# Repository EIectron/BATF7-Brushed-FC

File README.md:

# BATF7-Brushed-FC
 STM32F722 Based brushed flight controller board

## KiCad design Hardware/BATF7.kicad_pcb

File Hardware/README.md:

<div align="center">
  <b>
   <h1>
      BATF7
   </h1>
   <h6>
     V1
   </h6>
  </b>

</div>

Key Features
* ARM Cortex-M7 core F7 216 MHz CPU
* Invensense MPU-6500 Six-Axis (Gyro + Accelerometer) low power consumption MEMS MotionTracking™ Device
* Blackbox logging via onboard dataflash chip
* Battery polarity reversed connection protection. The fc board remains perfect even if you plug the battery in wrong way.
* Fully programmable through Betaflight, using the onboard USB port, tune all the parameters, PID's, and rates to your perfect settings
* Designed to work with current Whoop Drone or Blade Inductrix setups
* The flight controller board comes pre-flashed with Betaflight firmware, and pre-soldered 55mm power cable pigtail with JST-PH 2.0 connector, AKA PowerWhoop connector.

Specifications
* CPU: `STM32F411CEU6`
* Six-Axis: `MPU6500`
* ESC: All FETs are rated at 35A maximum. Support 6x15mm/7x20mm/8x20mm/8.5x20mm etc motors.
* Size: 29mm x 29mm, fully compatible with the Inductrix quad frame and mounting pattern
* Firmware version: Betaflight BATF7 3.5.0
* Power Cable: 55mm, with JST-PH 2.0 connector, AKA PowerWhoop connector
* Weight: 4.2g

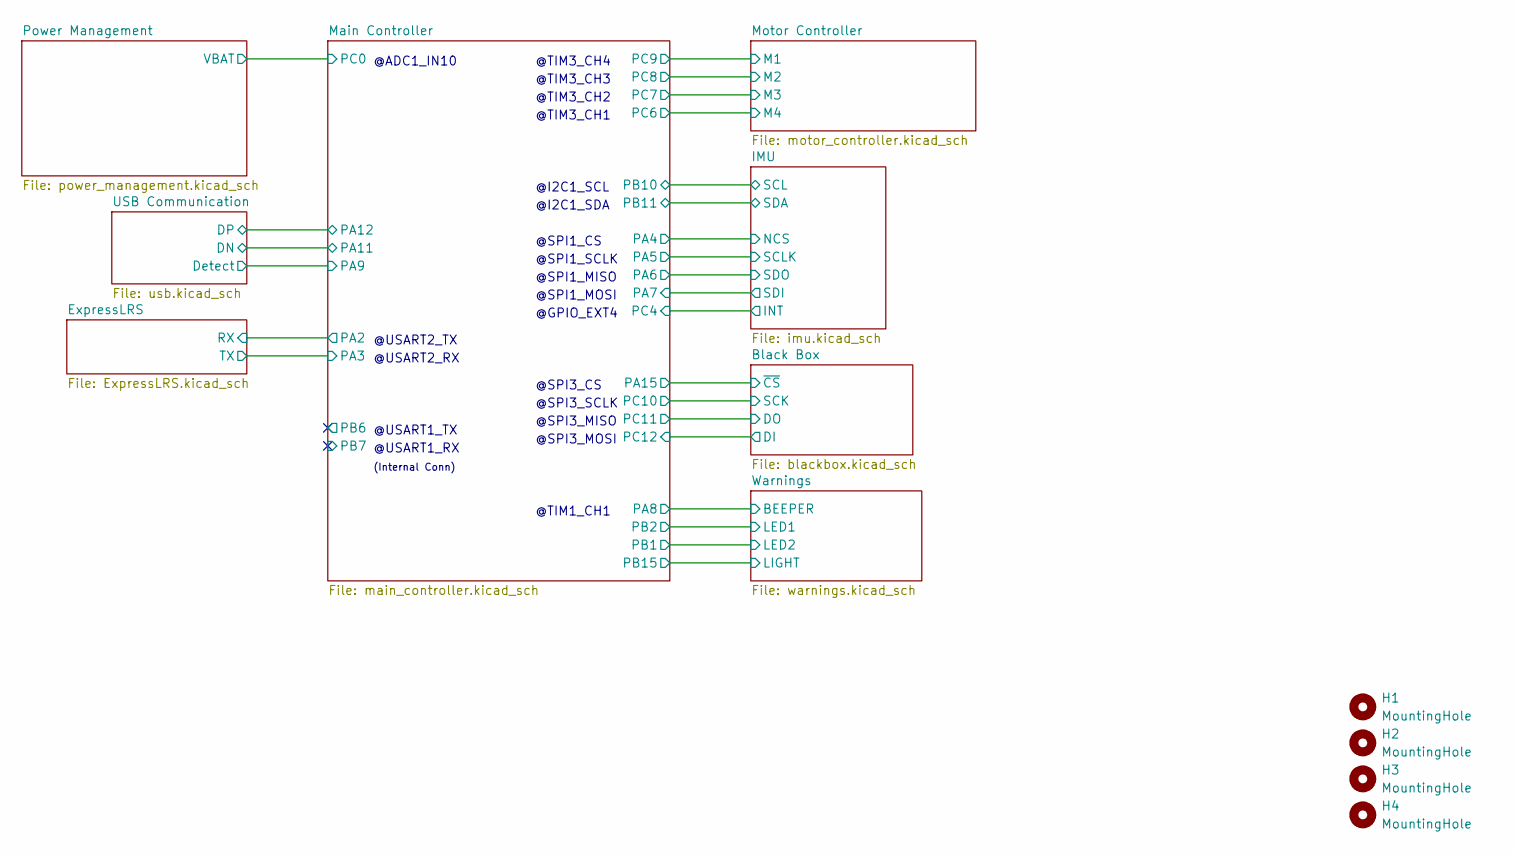
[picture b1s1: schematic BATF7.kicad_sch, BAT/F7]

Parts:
H1, H2, H3, H4: MountingHole; MH32

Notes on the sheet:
@ADC1_IN10
@USART1_RX
@TIM3_CH4
@USART2_TX
(Internal Conn)
@SPI3_SCLK
@USART1_TX
@TIM3_CH1
@SPI3_MOSI
@TIM1_CH1
@SPI3_MISO
@SPI1_MOSI
@I2C1_SDA
@TIM3_CH2
@I2C1_SCL
@SPI3_CS
@USART2_RX
@SPI1_MISO
@SPI1_CS
@TIM3_CH3
@SPI1_SCLK
@GPIO_EXT4

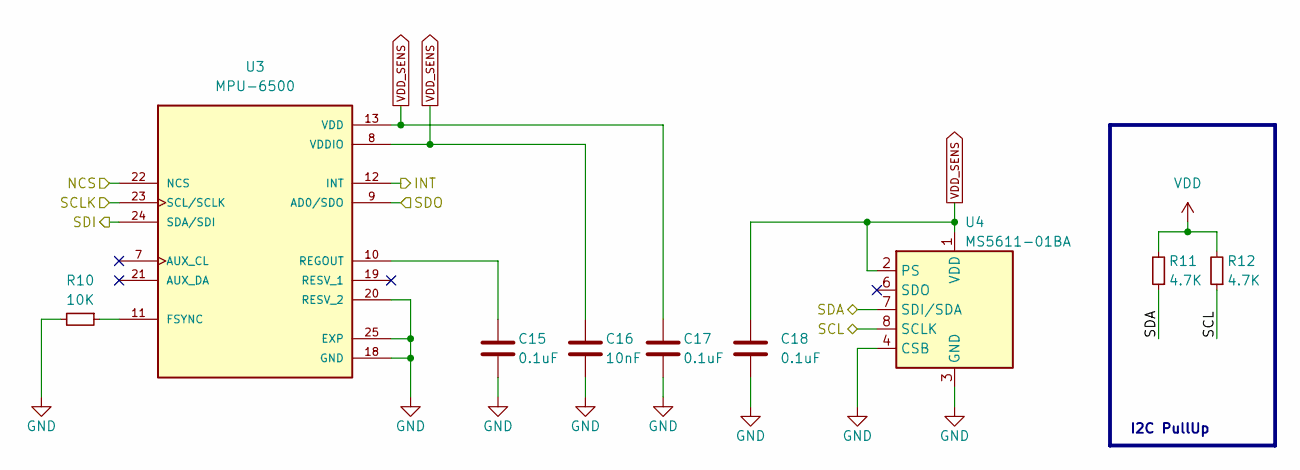
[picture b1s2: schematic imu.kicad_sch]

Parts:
C15, C17, C18: 0.1uF; C_0402_1005Metric
C16: 10nF; C_0402_1005Metric
R10: 10K; R_0402_1005Metric
R11, R12: 4.7K; R_0402_1005Metric
U3: MPU-6500; MPU6500
U4: MS5611-01BA; LGA-8_3x5mm_P1.25mm

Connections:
/IMU/SCL: R12.1, U4.8 (SCLK); also elsewhere on the board
/IMU/SDA: R11.1, U4.7 (SDI/SDA); also elsewhere on the board
/Main Controller/MPU_INT: U3.12 (INT); also elsewhere on the board
/Main Controller/SPI1_MISO: U3.9 (AD0/SDO); also elsewhere on the board
/Main Controller/SPI1_MOSI: U3.24 (SDA/SDI); also elsewhere on the board
/Main Controller/SPI1_SCK: U3.23 (SCL/SCLK); also elsewhere on the board
/Main Controller/SPI1_~CS: U3.22 (NCS); also elsewhere on the board
GND: C15.2, C16.1, C17.2, C18.2, R10.2, U3.18 (GND), U3.20 (RESV_2), U3.25 (EXP), U4.3 (GND), U4.4 (CSB), U4.5 (CSB); also elsewhere on the board
unnamed: R10.1, U3.11 (FSYNC)
unnamed: C15.1, U3.10 (REGOUT)
VDD: R11.2, R12.2; also elsewhere on the board
VDD_SENS: C16.2, C17.1, C18.1, U3.8 (VDDIO), U3.13 (VDD), U4.1 (VDD), U4.2 (PS); also elsewhere on the board

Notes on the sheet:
I2C PullUp

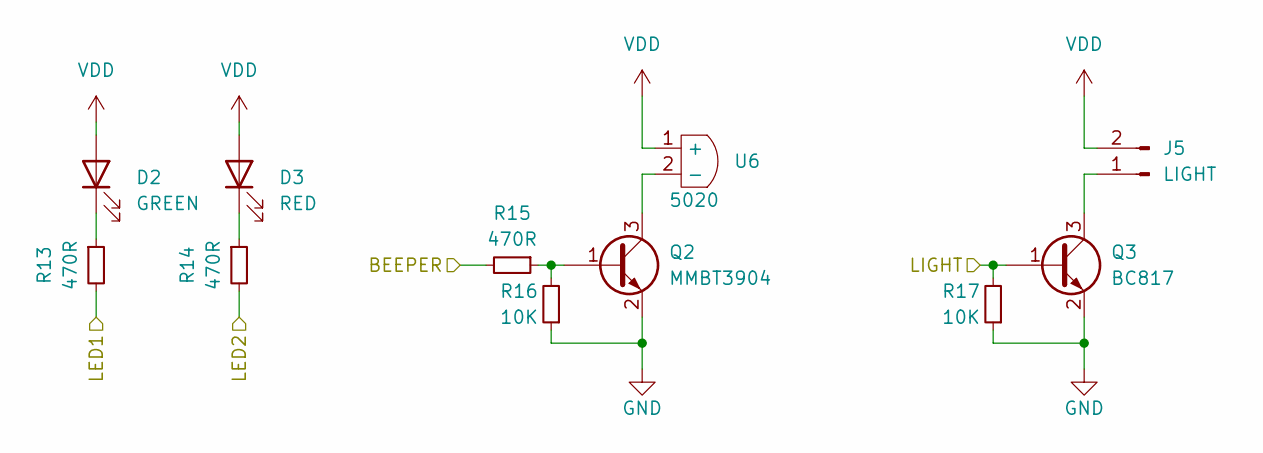
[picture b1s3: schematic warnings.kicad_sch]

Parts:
D2: GREEN; LED_0603_1608Metric
D3: RED; LED_0603_1608Metric
J5: LIGHT; C_0805_2012Metric
Q2: MMBT3904; SOT-23
Q3: BC817; SOT-23
R13, R14, R15: 470R; R_0402_1005Metric
R16, R17: 10K; R_0402_1005Metric
U6: 5020; ABMT-801-RC_PIEZO

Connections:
/Main Controller/BEEPER: R15.2; also elsewhere on the board
/Main Controller/LED1: R13.2; also elsewhere on the board
/Main Controller/LED2: R14.2; also elsewhere on the board
/Main Controller/LIGHT: Q3.1 (B), R17.2; also elsewhere on the board
GND: Q2.2 (E), Q3.2 (E), R16.1, R17.1; also elsewhere on the board
unnamed: D2.1 (K), R13.1
unnamed: D3.1 (K), R14.1
unnamed: J5.1, Q3.3 (C)
unnamed: Q2.1 (B), R15.1, R16.2
unnamed: Q2.3 (C), U6.2 (-)
VDD: D2.2 (A), D3.2 (A), J5.2, U6.1 (+); also elsewhere on the board

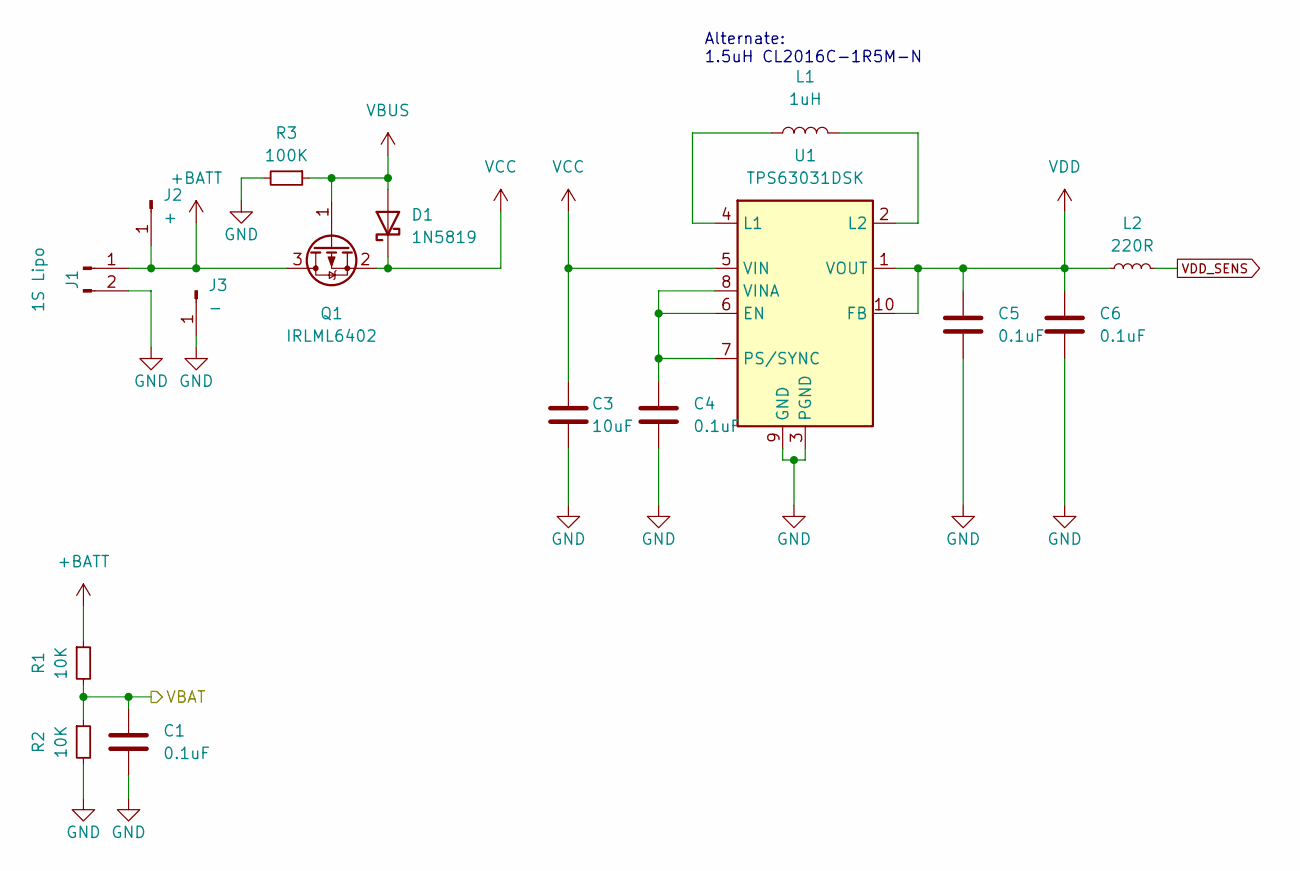
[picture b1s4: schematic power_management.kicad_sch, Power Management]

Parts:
C1, C4, C5, C6: 0.1uF; C_0402_1005Metric
C3: 10uF; C_0402_1005Metric
D1: 1N5819; SOD-323
J1: 1S Lipo; 1x02-Long-Pad
J2: +; TestPoint_THTPad_1.0x1.0mm_Drill0.5mm
J3: -; TestPoint_THTPad_1.0x1.0mm_Drill0.5mm
L1: 1uH; L_Murata_DFE201610P
L2: 220R; L_0603_1608Metric
Q1: IRLML6402; SOT-23
R1, R2: 10K; R_0402_1005Metric
R3: 100K; R_0402_1005Metric
U1: TPS63031DSK; WSON-10-1EP_2.5x2.5mm_P0.5mm_EP1.2x2mm

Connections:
+BATT: J1.1, J2.1, Q1.3 (D), R1.1; also elsewhere on the board
/Main Controller/VBAT_ADC: C1.1, R1.2, R2.1; also elsewhere on the board
GND: C1.2, C3.2, C4.2, C5.2, C6.2, J1.2, J3.1, R2.2, R3.2, U1.3 (PGND), U1.9 (GND), U1.11 (PGND); also elsewhere on the board
unnamed: C4.1, U1.6 (EN), U1.7 (PS/SYNC), U1.8 (VINA)
unnamed: L1.1, U1.4 (L1)
unnamed: L1.2, U1.2 (L2)
VBUS: D1.2 (A), Q1.1 (G), R3.1; also elsewhere on the board
VCC: C3.1, D1.1 (K), Q1.2 (S), U1.5 (VIN)
VDD: C5.1, C6.1, L2.1, U1.1 (VOUT), U1.10 (FB); also elsewhere on the board
VDD_SENS: L2.2; also elsewhere on the board

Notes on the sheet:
Alternate: 1.5uH CL2016C-1R5M-N

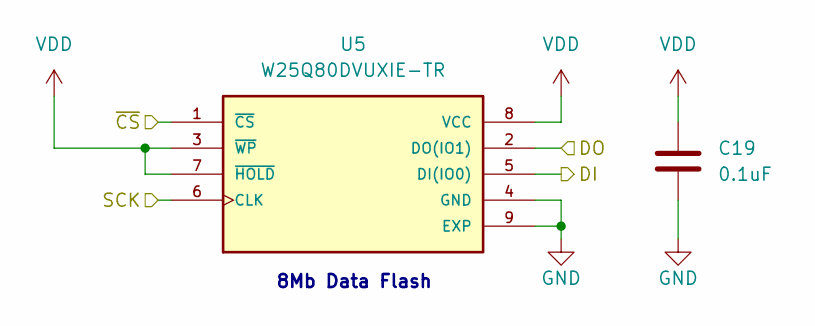
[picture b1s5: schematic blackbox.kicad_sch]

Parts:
C19: 0.1uF; C_0402_1005Metric
U5: W25Q80DVUXIE-TR; 8-USON

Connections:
/Main Controller/SPI3_MISO: U5.2 (DO(IO1)); also elsewhere on the board
/Main Controller/SPI3_MOSI: U5.5 (DI(IO0)); also elsewhere on the board
/Main Controller/SPI3_SCK: U5.6 (CLK); also elsewhere on the board
/Main Controller/SPI3_~CS: U5.1 (~CS); also elsewhere on the board
GND: C19.2, U5.4 (GND), U5.9 (EXP); also elsewhere on the board
VDD: C19.1, U5.3 (~WP), U5.7 (~HOLD), U5.8 (VCC); also elsewhere on the board

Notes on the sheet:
8Mb Data Flash

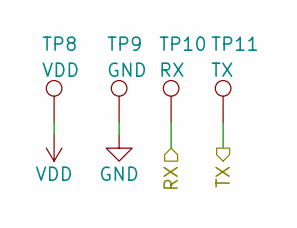
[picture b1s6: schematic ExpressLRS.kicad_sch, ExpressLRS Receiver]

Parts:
TP8: VDD; TestPoint_Pad_1.0x1.0mm
TP9: GND; TestPoint_Pad_D1.0mm
TP10: RX; TestPoint_Pad_D1.0mm
TP11: TX; TestPoint_Pad_D1.0mm

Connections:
/Main Controller/USART2_RX: TP11.1; also elsewhere on the board
/Main Controller/USART2_TX: TP10.1; also elsewhere on the board
GND: TP9.1; also elsewhere on the board
VDD: TP8.1; also elsewhere on the board

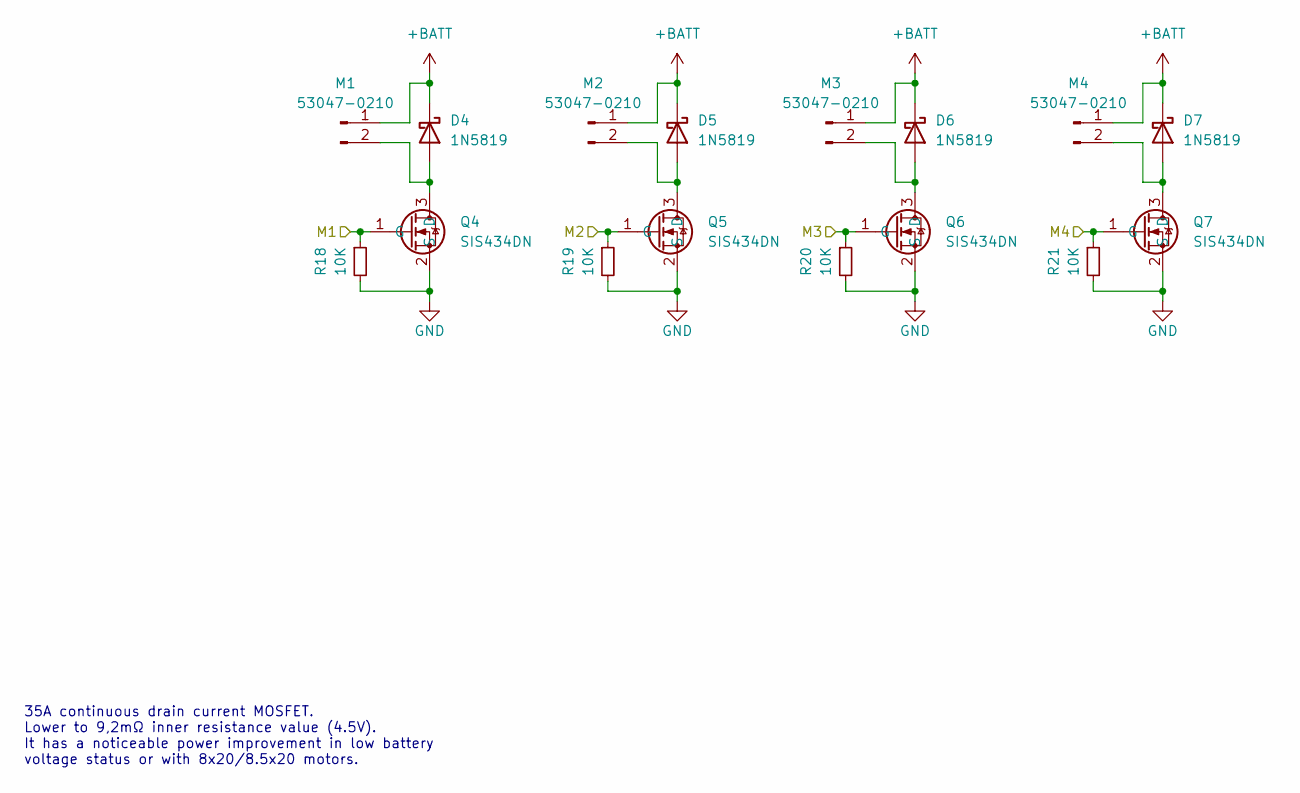
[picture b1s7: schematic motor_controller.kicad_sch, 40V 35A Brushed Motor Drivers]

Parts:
D4, D5, D6, D7: 1N5819; SOD-323
M1, M2, M3, M4: 53047-0210; Molex_PicoBlade_53047-0210_1x02_P1.25mm_Vertical
Q4, Q5, Q6, Q7: SIS434DN; PPAK1212-8
R18, R19, R20, R21: 10K; R_0402_1005Metric

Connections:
+BATT: D4.1 (K), D5.1 (K), D6.1 (K), D7.1 (K), M1.1, M2.1, M3.1, M4.1; also elsewhere on the board
/Main Controller/M1: Q4.1 (G), R18.1; also elsewhere on the board
/Main Controller/M2: Q5.1 (G), R19.1; also elsewhere on the board
/Main Controller/M3: Q6.1 (G), R20.1; also elsewhere on the board
/Main Controller/M4: Q7.1 (G), R21.1; also elsewhere on the board
GND: Q4.2 (S), Q5.2 (S), Q6.2 (S), Q7.2 (S), R18.2, R19.2, R20.2, R21.2; also elsewhere on the board
unnamed: D4.2 (A), M1.2, Q4.3 (D)
unnamed: D5.2 (A), M2.2, Q5.3 (D)
unnamed: D6.2 (A), M3.2, Q6.3 (D)
unnamed: D7.2 (A), M4.2, Q7.3 (D)

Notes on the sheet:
35A continuous drain current MOSFET. Lower to 9,2mΩ inner resistance value (4.5V). It has a noticeable power improvement in low battery voltage status or with 8x20/8.5x20 motors.

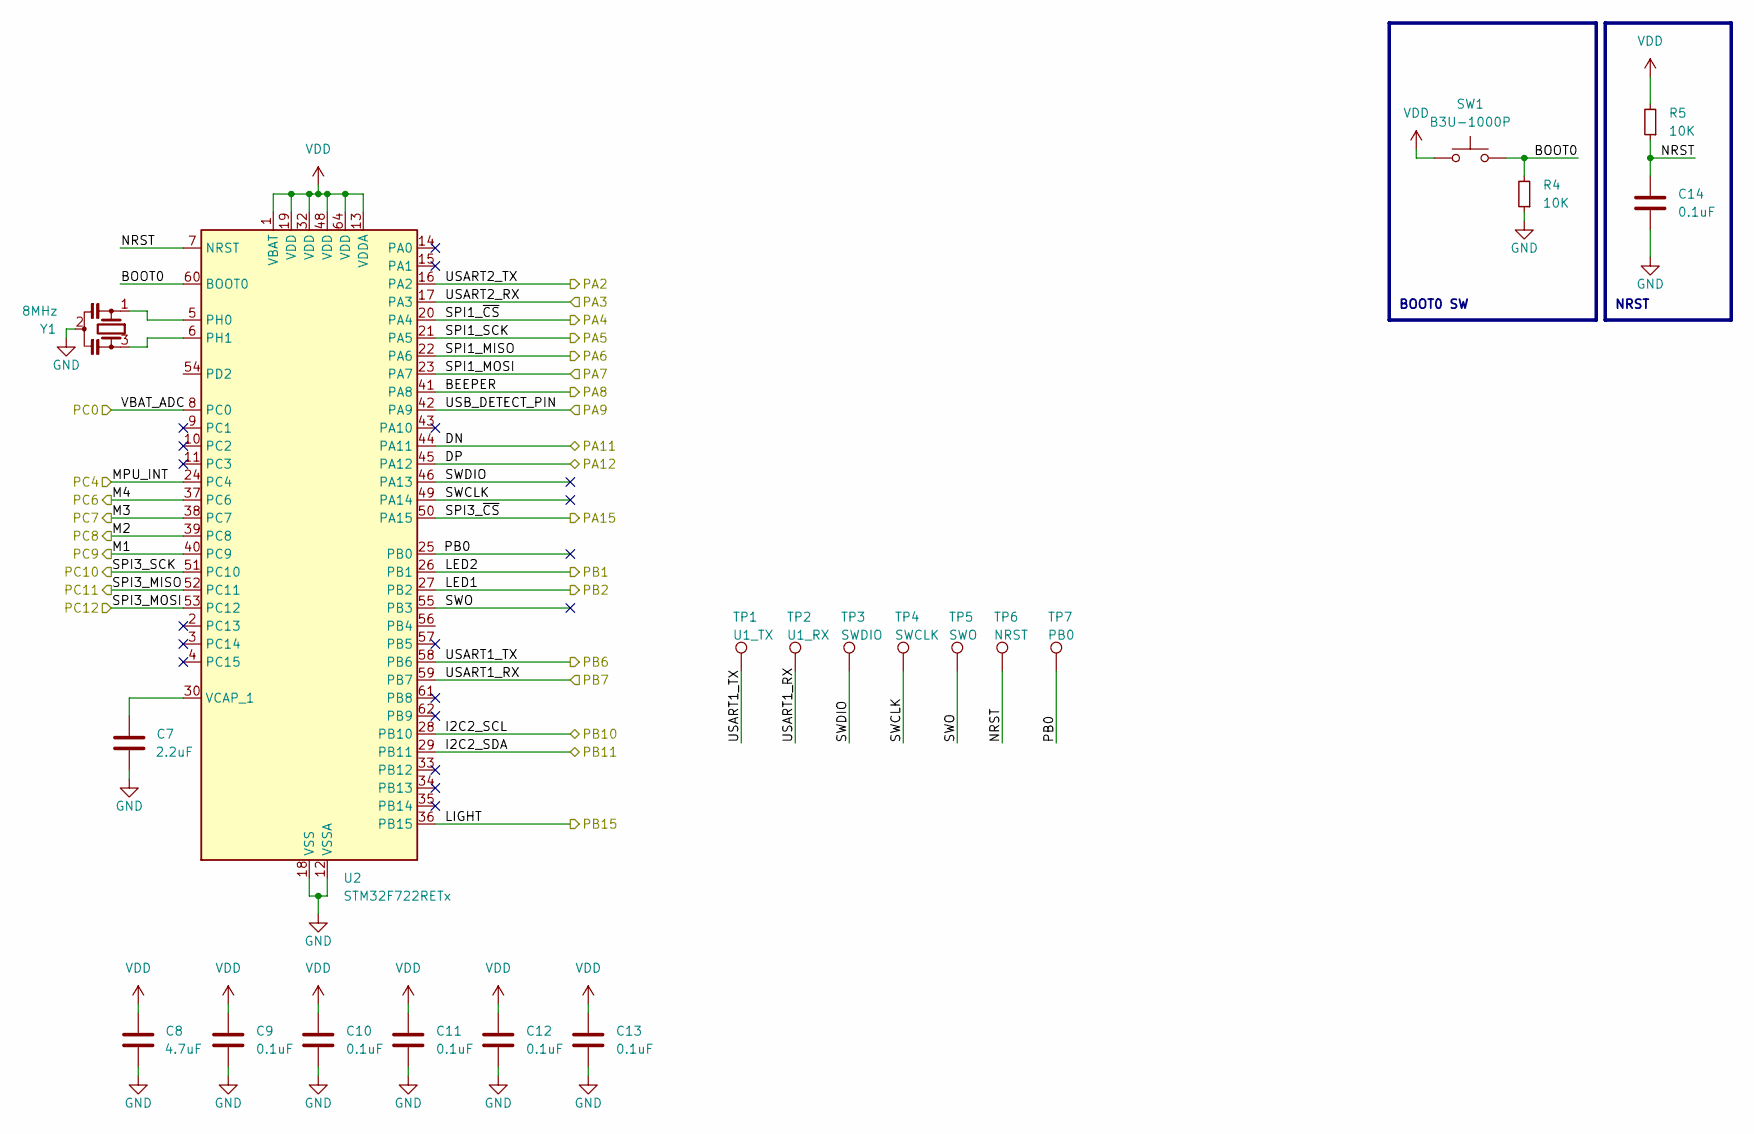
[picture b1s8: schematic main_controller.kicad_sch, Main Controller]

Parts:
C7: 2.2uF; C_0402_1005Metric
C8: 4.7uF; C_0402_1005Metric
C9, C10, C11, C12, C13, C14: 0.1uF; C_0402_1005Metric
R4, R5: 10K; R_0402_1005Metric
SW1: B3U-1000P; SW_SPST_B3U-1000P
TP1: U1_TX; TestPoint_Pad_D1.0mm
TP2: U1_RX; TestPoint_Pad_D1.0mm
TP3: SWDIO; TestPoint_Pad_D1.0mm
TP4: SWCLK; TestPoint_Pad_D1.0mm
TP5: SWO; TestPoint_Pad_D1.0mm
TP6: NRST; TestPoint_Pad_D1.0mm
TP7: PB0; TestPoint_Pad_D1.0mm
U2: STM32F722RETx; LQFP-64_10x10mm_P0.5mm
Y1: 8MHz; Resonator_SMD_Murata_CSTxExxV-3Pin_3.0x1.1mm

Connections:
/IMU/SCL: U2.28 (PB10); also elsewhere on the board
/IMU/SDA: U2.29 (PB11); also elsewhere on the board
/Main Controller/BEEPER: U2.41 (PA8); also elsewhere on the board
/Main Controller/BOOT0: R4.2, SW1.2, U2.60 (BOOT0)
/Main Controller/DN: U2.44 (PA11); also elsewhere on the board
/Main Controller/DP: U2.45 (PA12); also elsewhere on the board
/Main Controller/LED1: U2.27 (PB2); also elsewhere on the board
/Main Controller/LED2: U2.26 (PB1); also elsewhere on the board
/Main Controller/LIGHT: U2.36 (PB15); also elsewhere on the board
/Main Controller/M1: U2.40 (PC9); also elsewhere on the board
/Main Controller/M2: U2.39 (PC8); also elsewhere on the board
/Main Controller/M3: U2.38 (PC7); also elsewhere on the board
/Main Controller/M4: U2.37 (PC6); also elsewhere on the board
/Main Controller/MPU_INT: U2.24 (PC4); also elsewhere on the board
/Main Controller/NRST: C14.1, R5.1, TP6.1, U2.7 (NRST)
/Main Controller/PB0: TP7.1, U2.25 (PB0)
/Main Controller/SPI1_MISO: U2.22 (PA6); also elsewhere on the board
/Main Controller/SPI1_MOSI: U2.23 (PA7); also elsewhere on the board
/Main Controller/SPI1_SCK: U2.21 (PA5); also elsewhere on the board
/Main Controller/SPI1_~CS: U2.20 (PA4); also elsewhere on the board
/Main Controller/SPI3_MISO: U2.52 (PC11); also elsewhere on the board
/Main Controller/SPI3_MOSI: U2.53 (PC12); also elsewhere on the board
/Main Controller/SPI3_SCK: U2.51 (PC10); also elsewhere on the board
/Main Controller/SPI3_~CS: U2.50 (PA15); also elsewhere on the board
/Main Controller/SWCLK: TP4.1, U2.49 (PA14)
/Main Controller/SWDIO: TP3.1, U2.46 (PA13)
/Main Controller/SWO: TP5.1, U2.55 (PB3)
/Main Controller/USART1_RX: TP2.1, U2.59 (PB7)
/Main Controller/USART1_TX: TP1.1, U2.58 (PB6)
/Main Controller/USART2_RX: U2.17 (PA3); also elsewhere on the board
/Main Controller/USART2_TX: U2.16 (PA2); also elsewhere on the board
/Main Controller/USB_DETECT_PIN: U2.42 (PA9); also elsewhere on the board
/Main Controller/VBAT_ADC: U2.8 (PC0); also elsewhere on the board
GND: C7.2, C8.2, C9.2, C10.2, C11.2, C12.2, C13.2, C14.2, R4.1, U2.12 (VSSA), U2.18 (VSS), U2.31 (VSS), U2.47 (VSS), U2.63 (VSS), Y1.2; also elsewhere on the board
unnamed: U2.5 (PH0), Y1.1
unnamed: U2.6 (PH1), Y1.3
unnamed: C7.1, U2.30 (VCAP_1)
VDD: C8.1, C9.1, C10.1, C11.1, C12.1, C13.1, R5.2, SW1.1, U2.1 (VBAT), U2.13 (VDDA), U2.19 (VDD), U2.32 (VDD), U2.48 (VDD), U2.64 (VDD); also elsewhere on the board

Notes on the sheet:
NRST
BOOT0 SW

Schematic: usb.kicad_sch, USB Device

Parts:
F1: 500mA/6V; Fuse_0805_2012Metric
J4: 1051330011; USB_Micro-B_Molex-105133-0031
R6, R7: 22R %1; R_0402_1005Metric
R8: 15K %1; R_0402_1005Metric
R9: 22K %1; R_0402_1005Metric

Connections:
/Main Controller/DN: R7.1; also elsewhere on the board
/Main Controller/DP: R6.2; also elsewhere on the board
/Main Controller/USB_DETECT_PIN: R8.1, R9.2; also elsewhere on the board
/USB Communication/D+: J4.3 (D+), R6.1
/USB Communication/D-: J4.2 (D-), R7.2
GND: J4.5 (GND), J4.6 (Shield), R9.1; also elsewhere on the board
unnamed: F1.1, J4.1 (VBUS)
VBUS: F1.2, R8.2; also elsewhere on the board

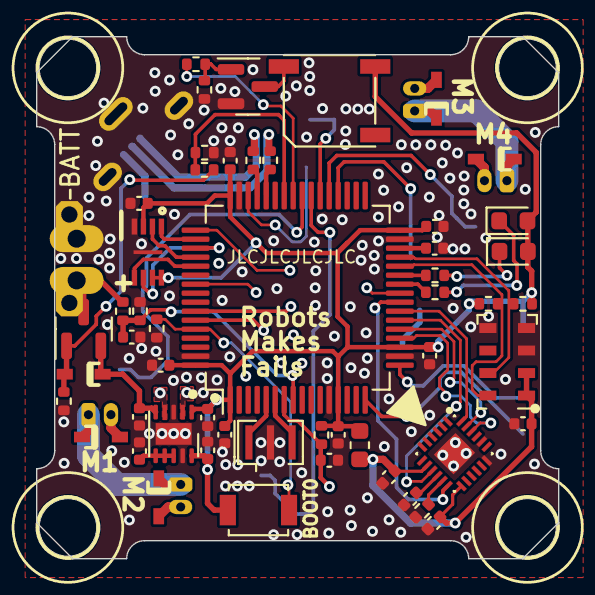
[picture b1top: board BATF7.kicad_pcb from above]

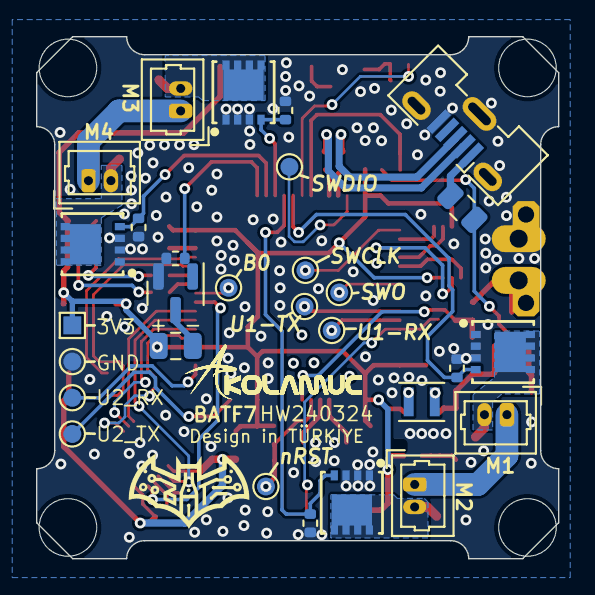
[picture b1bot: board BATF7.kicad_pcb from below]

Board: 4 copper layers, 29.0 x 29.0 mm, 88 parts (29 on the bottom side), 59 nets.

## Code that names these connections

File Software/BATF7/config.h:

/*
 * This file is part of Betaflight.
 *
 * Betaflight is free software. You can redistribute this software
 * and/or modify this software under the terms of the GNU General
 * Public License as published by the Free Software Foundation,
 * either version 3 of the License, or (at your option) any later
 * version.
 *
 * Betaflight is distributed in the hope that it will be useful,
 * but WITHOUT ANY WARRANTY; without even the implied warranty of
 * MERCHANTABILITY or FITNESS FOR A PARTICULAR PURPOSE.
 *
 * See the GNU General Public License for more details.
 *
 * You should have received a copy of the GNU General Public
 * License along with this software.
 *
 * If not, see <http://www.gnu.org/licenses/>.
 */

#pragma once

#define FC_TARGET_MCU     STM32F7X2
#define BOARD_NAME        BATF7
#define MANUFACTURER_ID   KLMC

#define USE_GYRO
#define GYRO_1_SPI_INSTANCE SPI1
#define USE_GYRO_SPI_MPU6500
#define USE_ACC
#define USE_ACC_SPI_MPU6500

#define USE_BARO
#define BARO_I2C_INSTANCE (I2CDEV_2)
#define USE_BARO_MS5611

#define USE_FLASH
#define FLASH_SPI_INSTANCE SPI3
#define USE_FLASH_W25Q128FV

#define USE_ADC
#define USE_I2C

#define BEEPER_PIN           PA8
#define MOTOR1_PIN           PC9
#define MOTOR2_PIN           PC8
#define MOTOR3_PIN           PC7
#define MOTOR4_PIN           PC6
#define UART1_TX_PIN         PB6
#define UART2_TX_PIN         PA2
#define UART1_RX_PIN         PB7
#define UART2_RX_PIN         PA3
#define I2C1_SCL_PIN         PB10
#define I2C1_SDA_PIN         PB11
#define LED0_PIN             PB2
#define LED1_PIN             PB1
#define SPI1_SCK_PIN         PA5
#define SPI3_SCK_PIN         PC10
#define SPI1_SDI_PIN         PA6
#define SPI3_SDI_PIN         PC11
#define SPI1_SDO_PIN         PA7
#define SPI3_SDO_PIN         PC12
#define ADC_VBAT_PIN         PC0
#define FLASH_CS_PIN         PA15
#define GYRO_1_EXTI_PIN      PC4
#define GYRO_1_CS_PIN        PA4
#define USB_DETECT_PIN       PA9

#define TIMER_PIN_MAPPING \
    TIMER_PIN_MAP( 0, MOTOR1_PIN , 1,  1) \
    TIMER_PIN_MAP( 1, MOTOR2_PIN , 1,  0) \
    TIMER_PIN_MAP( 2, MOTOR3_PIN , 1,  0) \
    TIMER_PIN_MAP( 3, MOTOR4_PIN , 1,  1) \
    TIMER_PIN_MAP( 4, BEEPER_PIN , 1,  0) \
    TIMER_PIN_MAP(12, PB9 , 1, -1)

#define DEFAULT_BLACKBOX_DEVICE     BLACKBOX_DEVICE_FLASH
#define ADC_INSTANCE ADC1
#define ADC1_DMA_OPT        0
#define DEFAULT_VOLTAGE_METER_SOURCE VOLTAGE_METER_ADC
#define BEEPER_PWM_HZ   4000
#define GYRO_1_ALIGN CW0_DEG
#define GYRO_1_ALIGN_YAW 0
#define BRUSHED_MOTORS

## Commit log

2024-04-10 Update
    add files
